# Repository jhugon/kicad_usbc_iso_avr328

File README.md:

# KiCad USB-C isolated ATmega328

A USB-C to serial converter connected through opto-isolators to an ATmega328.
Power for the isolated side comes through another USB-C port.

All runs on the 4V DC that comes through the USB ports and everything is
through-hole.

Notable parts are the USB-serial converter, a MCP2221A-I/P, the isolators,
ACPL-772L-000E, and the microcontroller, ATmega328P-PU.

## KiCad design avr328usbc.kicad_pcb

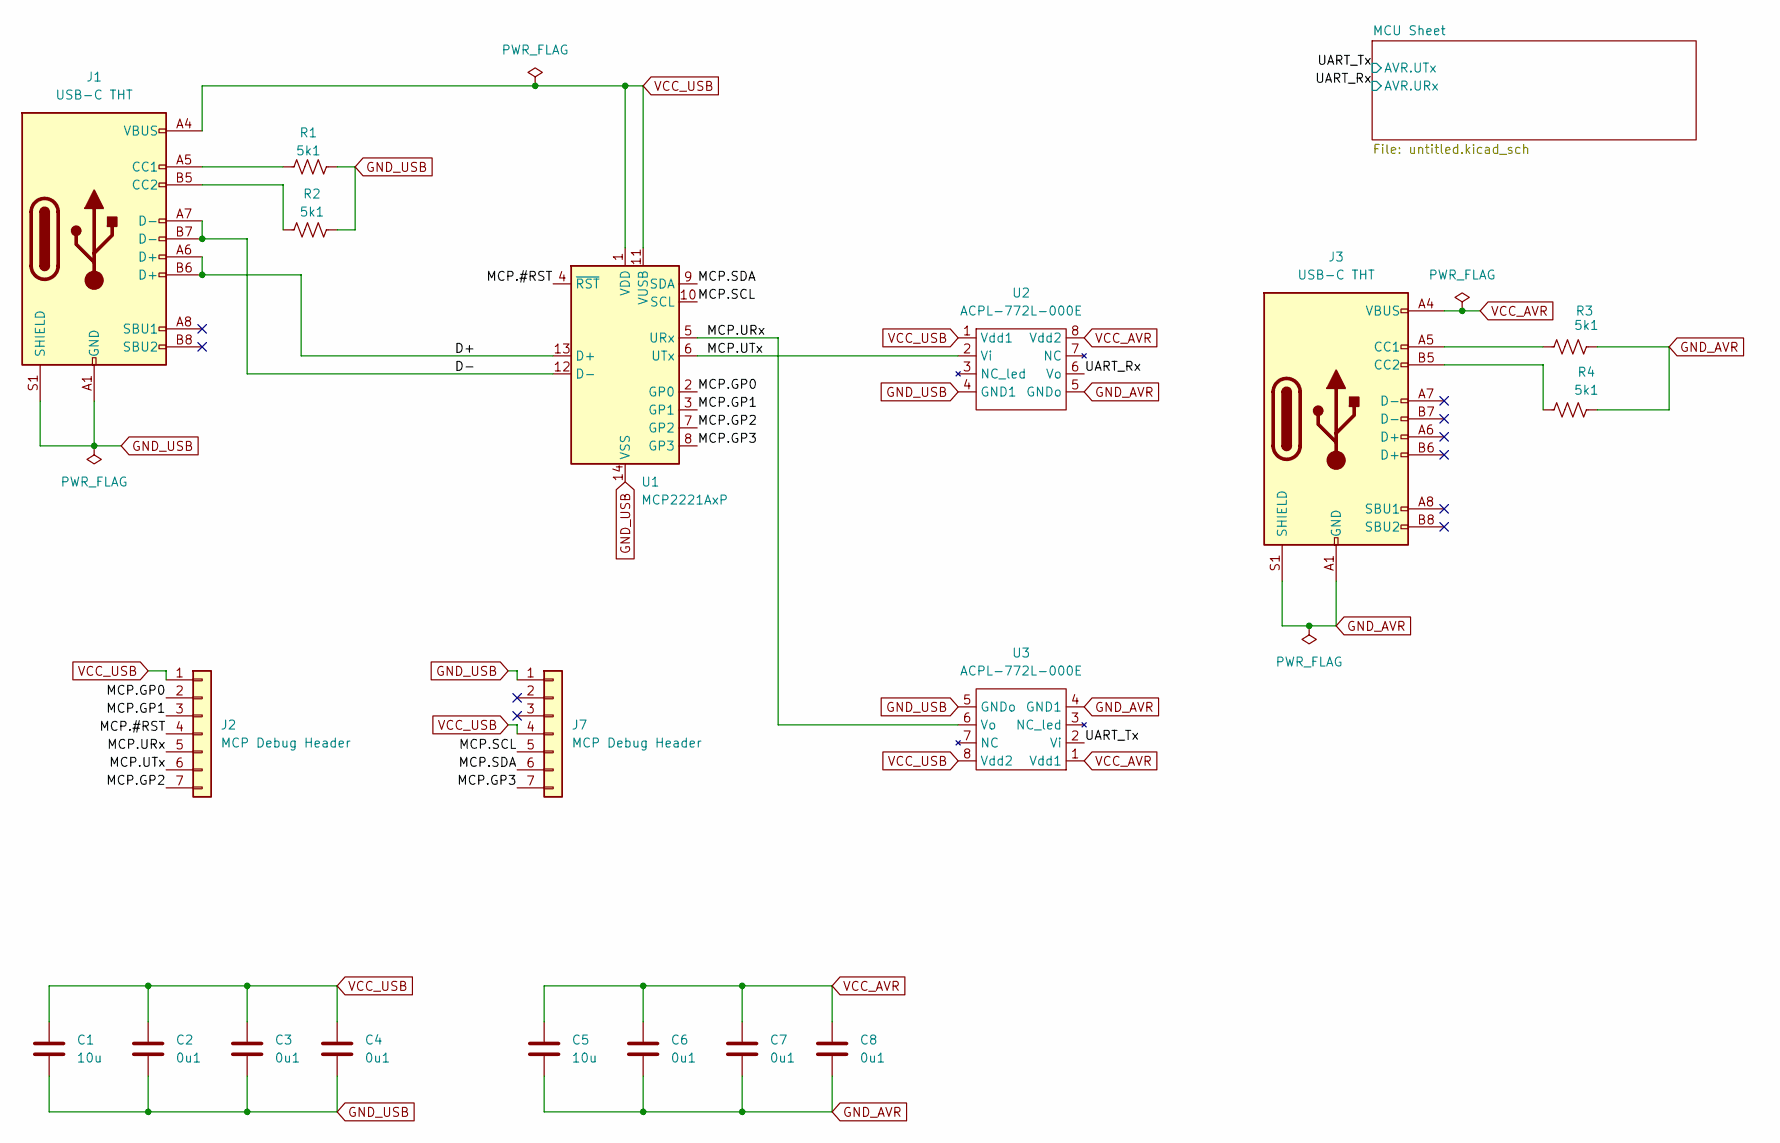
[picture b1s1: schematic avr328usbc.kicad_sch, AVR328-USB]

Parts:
C1, C5: 10u; C_Disc_D5.0mm_W2.5mm_P2.50mm; MFR Part Num FG14X7R1A106KRT00
C2, C3, C4, C6, C7, C8: 0u1; C_Disc_D5.0mm_W2.5mm_P2.50mm; MFR Part Num FG18X7R1H104KNT00
J1, J3: USB-C THT; USB_C_Receptacle_GCT_USB4085_Reduced_Pad_Size; MFR Part Num USB4085
J2, J7: MCP Debug Header; PinHeader_1x07_P2.54mm_Vertical; MFR Part Num 825433-7
R1, R2, R3, R4: 5k1; R_Axial_DIN0207_L6.3mm_D2.5mm_P7.62mm_Horizontal; MFR Part Num MF1/4LCT52R512J
U1: MCP2221AxP; DIP-14_W7.62mm; MFR Part Num MCP2221A-I/P
U2, U3: ACPL-772L-000E; DIP-8_W7.62mm; MFR Part Num ACPL-772L-000E

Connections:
/D+: J1.A6 (D+), J1.B6 (D+), U1.13 (D+)
/D-: J1.A7 (D-), J1.B7 (D-), U1.12 (D-)
/MCP.#RST: J2.4, U1.4 (~RST)
/MCP.GP0: J2.2, U1.2 (GP0)
/MCP.GP1: J2.3, U1.3 (GP1)
/MCP.GP2: J2.7, U1.7 (GP2)
/MCP.GP3: J7.7, U1.8 (GP3)
/MCP.SCL: J7.5, U1.10 (SCL)
/MCP.SDA: J7.6, U1.9 (SDA)
/MCP.URx: J2.5, U1.5 (URx), U3.6 (Vo)
/MCP.UTx: J2.6, U1.6 (UTx), U2.2 (Vi)
/UART_Rx: U2.6 (Vo); also elsewhere on the board
/UART_Tx: U3.2 (Vi); also elsewhere on the board
GND_AVR: C5.1, C6.1, C7.1, C8.1, J3.A1 (GND), J3.A12 (GND), J3.B1 (GND), J3.B12 (GND), J3.S1 (SHIELD), R3.2, R4.2, U2.5 (GNDo), U3.4 (GND1); also elsewhere on the board
GND_USB: C1.1, C2.1, C3.1, C4.1, J1.A1 (GND), J1.A12 (GND), J1.B1 (GND), J1.B12 (GND), J1.S1 (SHIELD), J7.1, R1.2, R2.2, U1.14 (VSS), U2.4 (GND1), U3.5 (GNDo)
unnamed: J1.A5 (CC1), R1.1
unnamed: J1.B5 (CC2), R2.1
unnamed: J3.A5 (CC1), R3.1
unnamed: J3.B5 (CC2), R4.1
VCC_AVR: C5.2, C6.2, C7.2, C8.2, J3.A4 (VBUS), J3.A9 (VBUS), J3.B4 (VBUS), J3.B9 (VBUS), U2.8 (Vdd2), U3.1 (Vdd1); also elsewhere on the board
VCC_USB: C1.2, C2.2, C3.2, C4.2, J1.A4 (VBUS), J1.A9 (VBUS), J1.B4 (VBUS), J1.B9 (VBUS), J2.1, J7.4, U1.1 (VDD), U1.11 (VUSB), U2.1 (Vdd1), U3.8 (Vdd2)

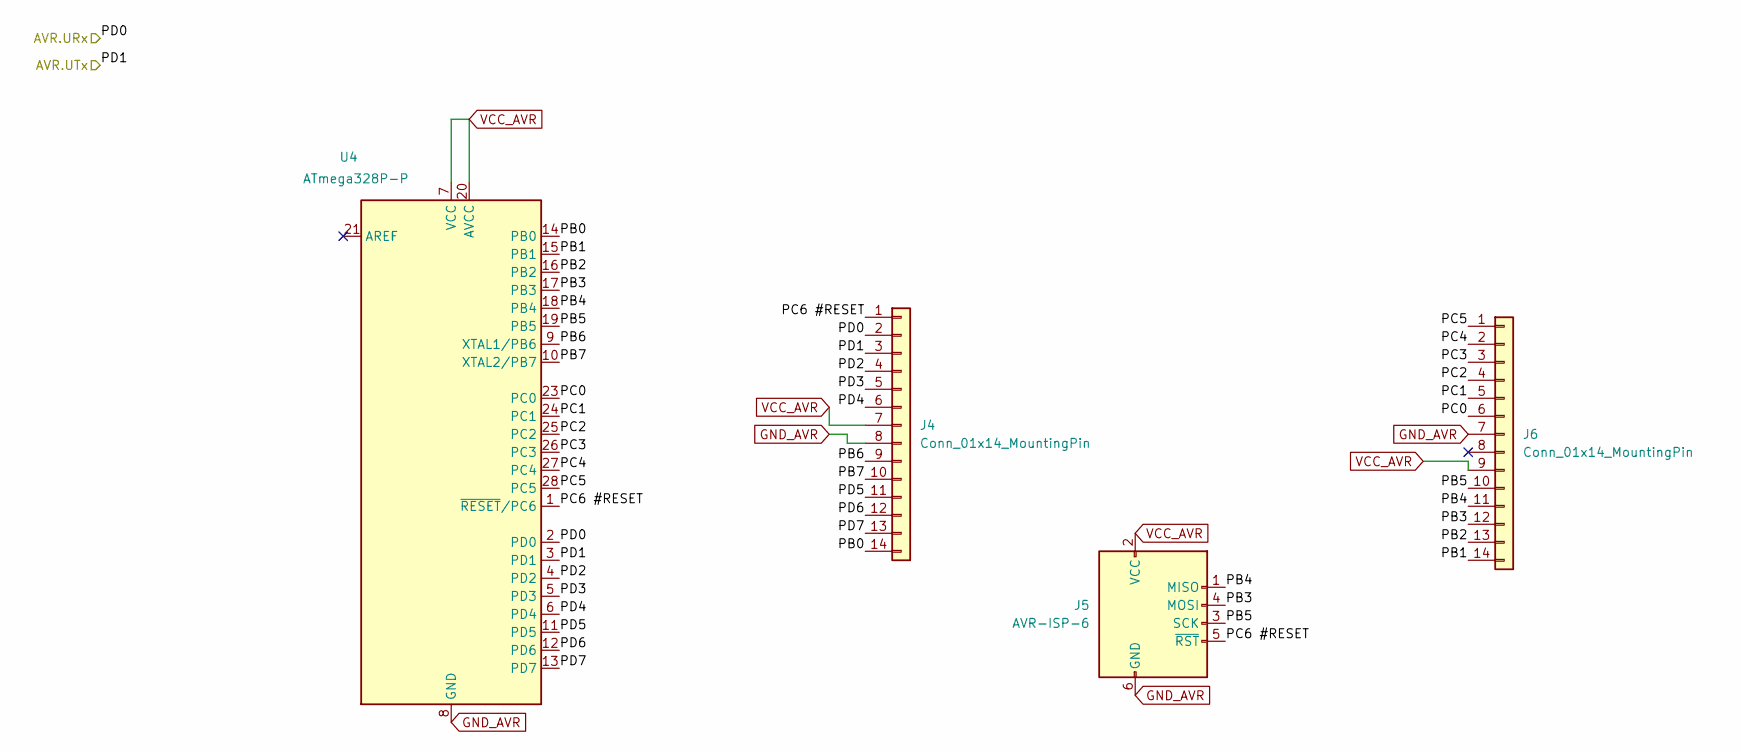
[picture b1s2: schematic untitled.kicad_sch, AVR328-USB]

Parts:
J4, J6: Conn_01x14_MountingPin; PinHeader_1x14_P2.54mm_Vertical
J5: AVR-ISP-6; PinHeader_2x03_P2.54mm_Vertical
U4: ATmega328P-P; DIP-28_W7.62mm; MFR Part Num ATmega328P-PU

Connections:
/MCU Sheet/PB0: J4.14, U4.14 (PB0)
/MCU Sheet/PB1: J6.14, U4.15 (PB1)
/MCU Sheet/PB2: J6.13, U4.16 (PB2)
/MCU Sheet/PB3: J5.4 (MOSI), J6.12, U4.17 (PB3)
/MCU Sheet/PB4: J5.1 (MISO), J6.11, U4.18 (PB4)
/MCU Sheet/PB5: J5.3 (SCK), J6.10, U4.19 (PB5)
/MCU Sheet/PB6: J4.9, U4.9 (XTAL1/PB6)
/MCU Sheet/PB7: J4.10, U4.10 (XTAL2/PB7)
/MCU Sheet/PC0: J6.6, U4.23 (PC0)
/MCU Sheet/PC1: J6.5, U4.24 (PC1)
/MCU Sheet/PC2: J6.4, U4.25 (PC2)
/MCU Sheet/PC3: J6.3, U4.26 (PC3)
/MCU Sheet/PC4: J6.2, U4.27 (PC4)
/MCU Sheet/PC5: J6.1, U4.28 (PC5)
/MCU Sheet/PC6 #RESET: J4.1, J5.5 (~RST), U4.1 (~RESET/PC6)
/MCU Sheet/PD2: J4.4, U4.4 (PD2)
/MCU Sheet/PD3: J4.5, U4.5 (PD3)
/MCU Sheet/PD4: J4.6, U4.6 (PD4)
/MCU Sheet/PD5: J4.11, U4.11 (PD5)
/MCU Sheet/PD6: J4.12, U4.12 (PD6)
/MCU Sheet/PD7: J4.13, U4.13 (PD7)
/UART_Rx: J4.2, U4.2 (PD0); also elsewhere on the board
/UART_Tx: J4.3, U4.3 (PD1); also elsewhere on the board
GND_AVR: J4.8, J5.6 (GND), J6.7, U4.8 (GND), U4.22 (GND); also elsewhere on the board
VCC_AVR: J4.7, J5.2 (VCC), J6.9, U4.7 (VCC), U4.20 (AVCC); also elsewhere on the board

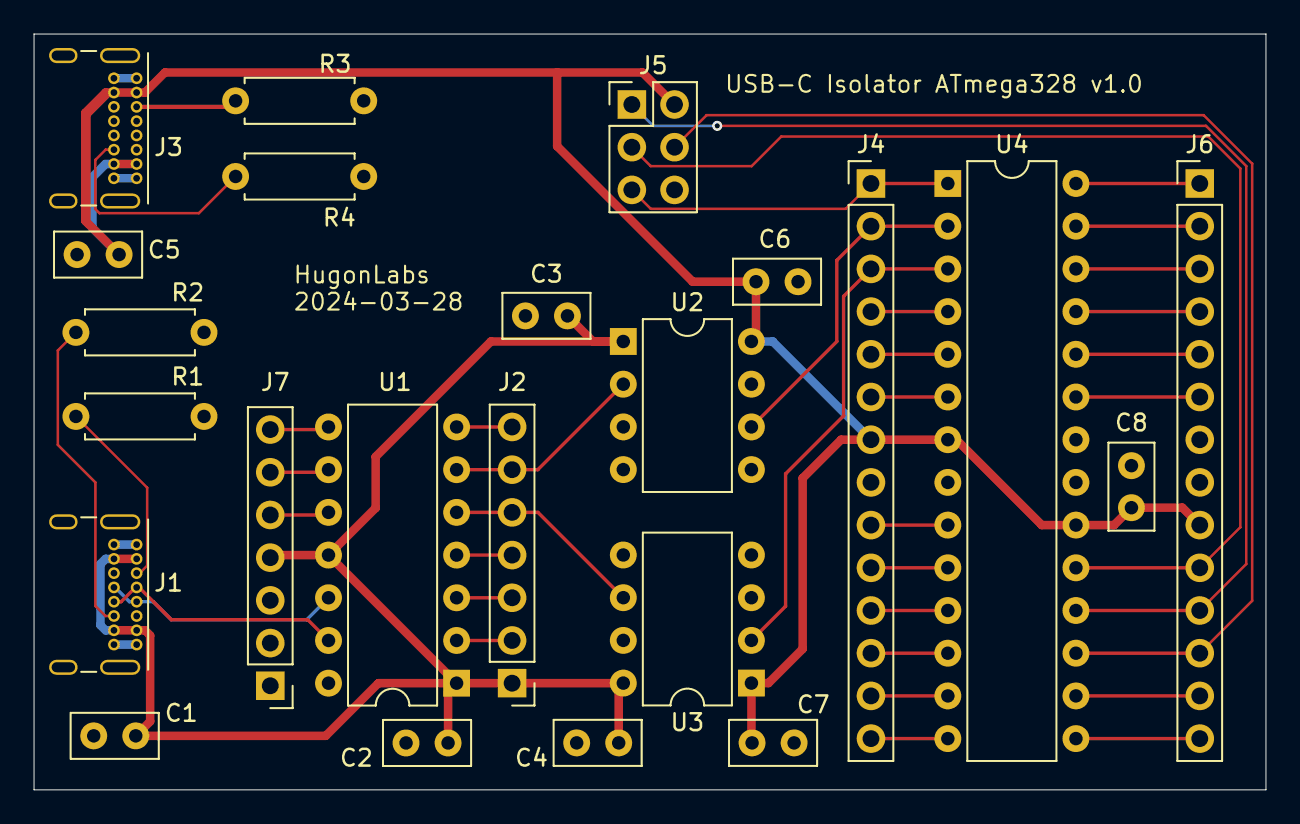
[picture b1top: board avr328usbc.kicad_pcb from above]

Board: 2 copper layers, 73.3 x 45.0 mm, 23 parts (0 on the bottom side), 42 nets.

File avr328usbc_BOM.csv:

"Reference","Value","Datasheet","Footprint","Qty","DNP","Description","MFR Part Num","MFR"
"C1,C5","10u","~","Capacitor_THT:C_Disc_D5.0mm_W2.5mm_P2.50mm","2","","Unpolarized capacitor","FG14X7R1A106KRT00","TDK"
"C2,C3,C4,C6,C7,C8","0u1","~","Capacitor_THT:C_Disc_D5.0mm_W2.5mm_P2.50mm","6","","Unpolarized capacitor","FG18X7R1H104KNT00","TDK"
"J1,J3","USB-C THT","https://www.usb.org/sites/default/files/documents/usb_type-c.zip","AAAA_Project_Library:USB_C_Receptacle_GCT_USB4085_Reduced_Pad_Size","2","","USB 2.0-only 16P Type-C Receptacle connector","USB4085","GCT"
"J2,J7","MCP Debug Header","~","Connector_PinHeader_2.54mm:PinHeader_1x07_P2.54mm_Vertical","2","DNP","Generic connector, single row, 01x07, script generated (kicad-library-utils/schlib/autogen/connector/)","9-146280-0","TE Connectivity"
"J4,J6","Conn_01x14_MountingPin","~","Connector_PinHeader_2.54mm:PinHeader_1x14_P2.54mm_Vertical","2","DNP","Generic connector, single row, 01x14, script generated (kicad-library-utils/schlib/autogen/connector/)","9-146280-0","TE Connectivity"
"J5","AVR-ISP-6"," ~","Connector_PinHeader_2.54mm:PinHeader_2x03_P2.54mm_Vertical","1","","Atmel 6-pin ISP connector","TE Connectivity","Molex"
"R1,R2,R3,R4","5k1","~","Resistor_THT:R_Axial_DIN0207_L6.3mm_D2.5mm_P7.62mm_Horizontal","4","","20% or better from USB Spec"," MF1/4LCT52R512J","KOA Speer"
"U1","MCP2221AxP","http://ww1.microchip.com/downloads/en/DeviceDoc/20005565B.pdf","Package_DIP:DIP-14_W7.62mm","1","","USB to I2C/UART Protocol Converter with GPIO, DIP-14","MCP2221A-I/P","Microchip"
"U2,U3","ACPL-772L-000E","https://www.broadcom.com/products/optocouplers/industrial-pl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","Package_DIP:DIP-8_W7.62mm","2","","High Speed CMOS Optocoupler in DIP 8","ACPL-772L-000E","Broadcom"
"U4","ATmega328P-P","http://ww1.microchip.com/downloads/en/DeviceDoc/ATmega328_P%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","Package_DIP:DIP-28_W7.62mm","1","","20MHz, 32kB Flash, 2kB SRAM, 1kB EEPROM, DIP-28","ATmega328P-PU","Microchip"

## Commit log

2024-03-04 initial commit of project
    schematic has some work done
2024-03-07 schematic: added a bunch of labels & changed pwer to labels
2024-03-08 added mcu sheet and global labels for power
2024-03-08 sch: finished with main components
2024-03-08 sch: done, footprints added as well
2024-03-08 working on pcb
2024-03-27 finished converting schematic to correct USBC and pin headers
    Symbols didn't match the footprints
2024-03-27 pcb footprints placed and locked
2024-03-28 added more detail to BOM for resistors/caps
2024-03-28 routed most non-header signals
2024-03-28 reordered pins and routed MCP header
2024-03-28 changed AVR header into 2 headers mirroring pinout
2024-03-28 changed MCP header into two headers mirroring part
    also rearanged components on board
2024-03-28 much of board routed
2024-03-28 first pass at ground plane
2024-03-28 after first look at DRC
2024-03-28 modified USB-C footprint to follow clearence rules at OSH
    Now almost all DRCs pass
2024-03-28 Removed off-board silk from USB and tweaked silk refid pos
    No more silk warnings or errors!
2024-03-28 Added silk text to board
2024-03-28 final version edits
2024-03-28 Add schematic, pcb, and render jpgs/pdfs
2024-03-29 Finished and exported BOM
2024-03-29 fixed bug in BOM
2024-04-03 Add README.md
2024-04-03 Added render images to readme
